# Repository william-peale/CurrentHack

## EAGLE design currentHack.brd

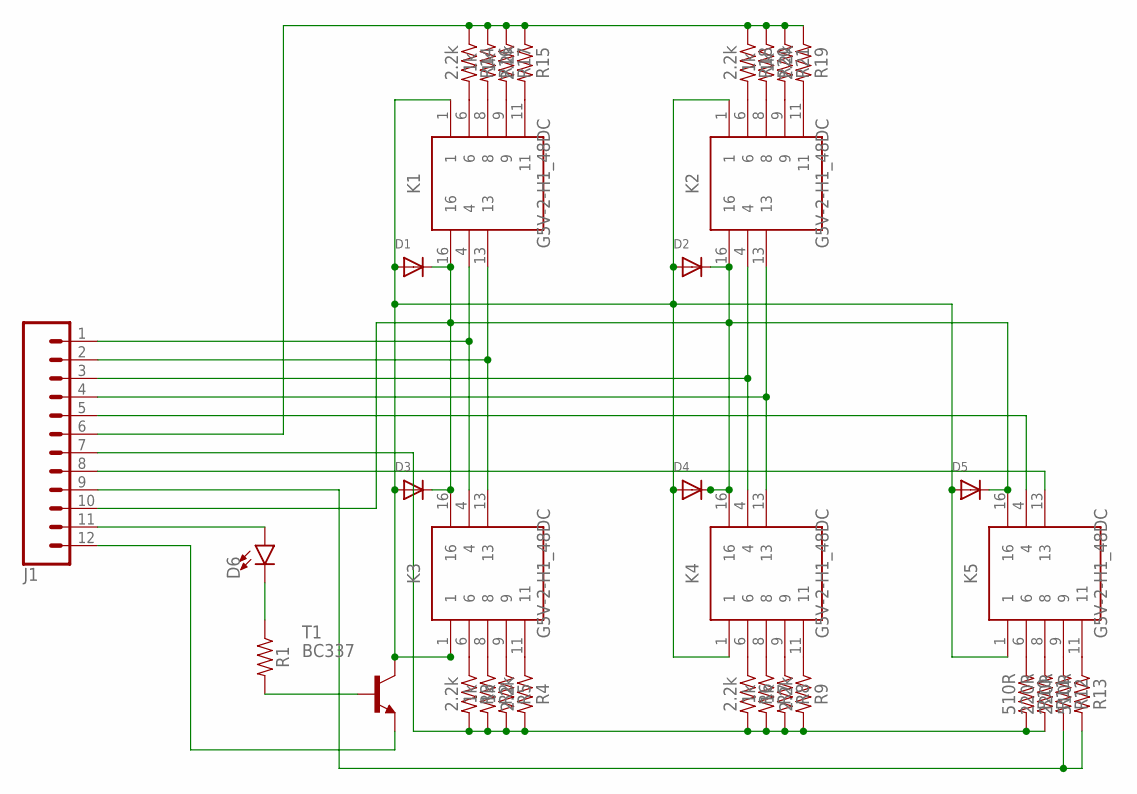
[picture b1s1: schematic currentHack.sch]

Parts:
D1, D2, D3, D4, D5: DIODEDO-1N4148; DO-1N4148
D6: LED3MM; LED_3MM
J1: CONN_12; 1X12
K1, K2, K3, K4, K5: G5V-2-H1_48DC; G5V-2-H1
R1: AXIAL-0.3
R2, R5, R7, R8, R16, R17, R20, R21: 1k; AXIAL-0.3
R3, R4, R6, R9, R14, R15, R18, R19: 2.2k; AXIAL-0.3
R10, R13: 510R; AXIAL-0.3
R11, R12: 220R; AXIAL-0.3
T1: BC337; TO92

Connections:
unnamed: J1.3, K2.4, K4.4
unnamed: J1.1, K1.4, K3.4
unnamed: J1.2, K1.13, K3.13
unnamed: J1.4, K2.13, K4.13
unnamed: D6.A, J1.11
unnamed: D6.K (C), R1.P$1 (1)
unnamed: R1.P$2 (2), T1.2 (B)
unnamed: D1.A, D2.A, D3.A, D4.A, D5.A, K1.1, K2.1, K3.1, K4.1, K5.1, T1.3 (C)
unnamed: K5.6, R10.P$1 (1)
unnamed: D1.C, D2.C, D3.C, D4.C, D5.C, J1.10, K1.16, K2.16, K3.16, K4.16, K5.16
unnamed: K5.8, R11.P$1 (1)
unnamed: K5.9, R12.P$1 (1)
unnamed: K5.11, R13.P$1 (1)
unnamed: K1.6, R14.P$2 (2)
unnamed: K1.11, R15.P$2 (2)
unnamed: K1.8, R16.P$2 (2)
unnamed: K1.9, R17.P$2 (2)
unnamed: J1.8, K5.13
unnamed: J1.5, K5.4
unnamed: J1.12, T1.1 (E)
unnamed: K3.8, R2.P$1 (1)
unnamed: K3.6, R3.P$1 (1)
unnamed: K3.11, R4.P$1 (1)
unnamed: K3.9, R5.P$1 (1)
unnamed: K4.6, R6.P$1 (1)
unnamed: K4.8, R7.P$1 (1)
unnamed: K4.9, R8.P$1 (1)
unnamed: K4.11, R9.P$1 (1)
unnamed: J1.7, R2.P$2 (2), R3.P$2 (2), R4.P$2 (2), R5.P$2 (2), R6.P$2 (2), R7.P$2 (2), R8.P$2 (2), R9.P$2 (2), R10.P$2 (2), R11.P$2 (2)
unnamed: J1.9, R12.P$2 (2), R13.P$2 (2)
unnamed: J1.6, R14.P$1 (1), R15.P$1 (1), R16.P$1 (1), R17.P$1 (1), R18.P$1 (1), R19.P$1 (1), R20.P$1 (1), R21.P$1 (1)
unnamed: K2.8, R20.P$2 (2)
unnamed: K2.6, R18.P$2 (2)
unnamed: K2.11, R19.P$2 (2)
unnamed: K2.9, R21.P$2 (2)

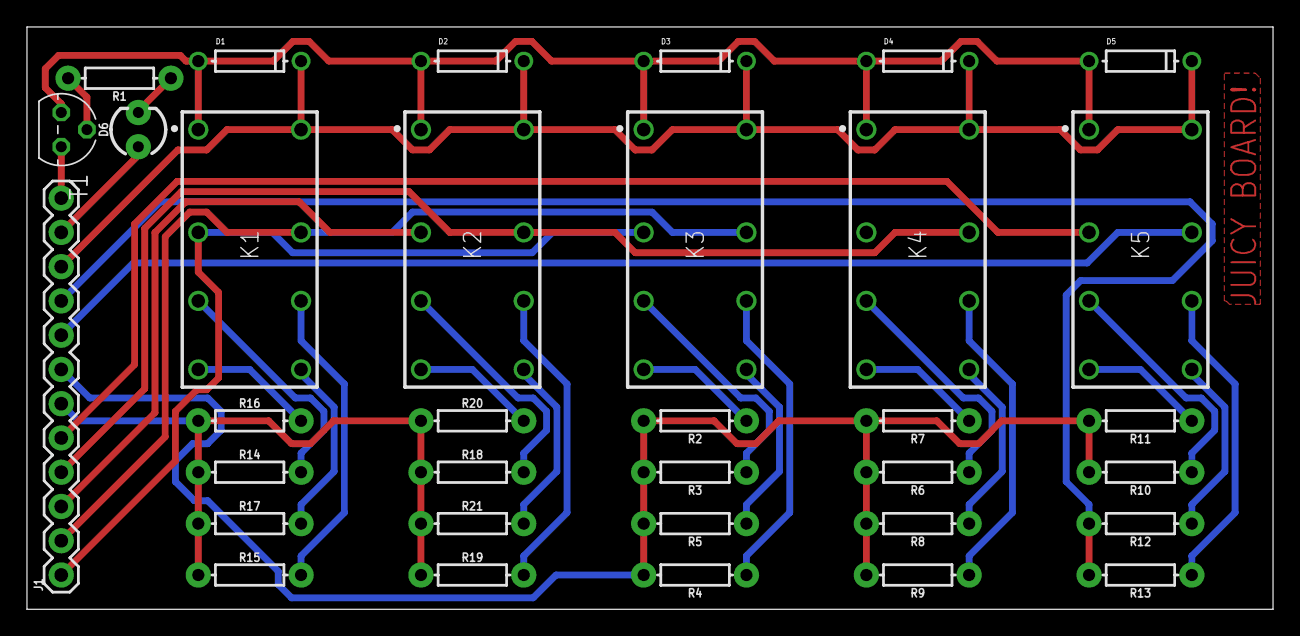
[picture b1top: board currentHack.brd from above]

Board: 2 copper layers, 92.4 x 43.2 mm, 34 parts (0 on the bottom side), 35 nets.

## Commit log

2018-02-15 added files

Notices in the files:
parts and their libraries:
SparkFun-LED: Licensing: Creative Commons ShareAlike 4.0 International - https://creativecommons.org/licenses/by-sa/4.0
